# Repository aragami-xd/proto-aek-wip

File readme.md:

Yeah so this pic said it all, but I swear it's a board this time and not just a pcb

<sub>*pic credit to Pat from TapTap discord, who stole it off reddit*</sub>

<br>
<br>

### FRL

It's an FRL cuz cbf dealing with aek f row. This is like **rev 5** of the design now

pics rendered from keyshot with a *sekrit tm* design

pics from fusion. can somewhat see the mounting points and the db from the pic

<br>
<br>

### Progress
- case: pretty much done at this point
- solenoid: solenoid compartment done, solenoid driver and power delivery circuitry still sus af, db compartment kinda done
- backplate: done
- alps pcb: routing and schematic done, just need to put in the reference for the diodes and any bit of clean up left
- alps plate: probably done
- SI pcb: routing and schematic done, just need to put in the reference for the diodes and any bit of clean up left
- SI plate: not started yet, probably easy (just need to figure out stabs mount)

TODO:
- find amber alps
- find sussy aek for the caps
- make sure stuff work
- buy solenoids
- cry looking at wallet

<br>
<br>

Also credit to clickpig for naming this board "**halfpipe**". Damn the original drawing in paint was bad

Credits to:
- all snazgs memebers: phoenix (for board hunting & designing), harky & joshajohnson (for pcb), veebee (them for pcb and case designs), gok & awwyaeh (for some design inputs), pigu (for being good lad, please come back dude), clickpig (for the name lmao, and being good lad), along with many other good lads
- ai03's keyboard atelier members: zlane (for some advise and tutorials), oreo (for aek project)
- blacksimoan server members: bitten eite (for solenoid recoomendations), simoan (for the server), the recap team (for blacksimon.tv/recap), and the weeb-nsfw posters, and the vints channel regulars

Engravings (potentially):
- theremingoatimpersonator.com
- :peeposmiel: (slightly tilted) for pigu
- prototype 7frl 'halfpipe'
- ara original artisanal design craft work studio tm r c sm

Old pics of prev designs, see prev commits or the pics/old folder

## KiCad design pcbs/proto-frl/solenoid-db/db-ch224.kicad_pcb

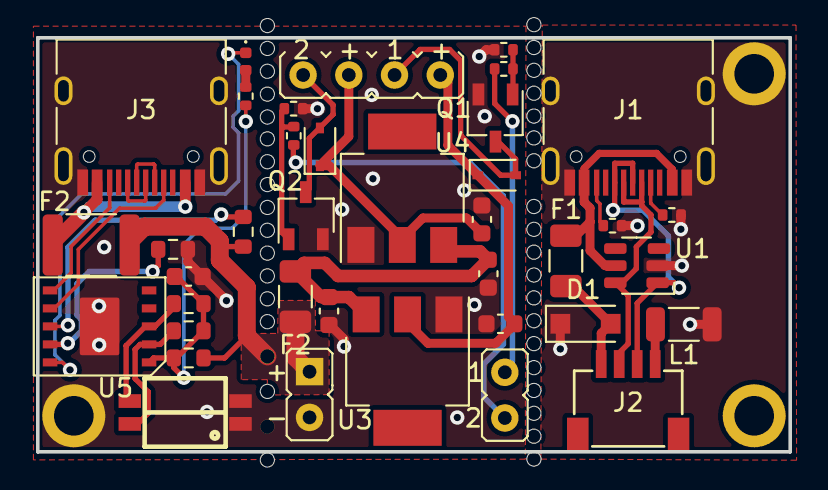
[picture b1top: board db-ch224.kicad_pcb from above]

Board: 2 copper layers, 41.8 x 23.0 mm, 38 parts (0 on the bottom side), 22 nets.

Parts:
C1, C2, C3, C4: 10uF; C_0603_1608Metric
C5: 1uF; C_0603_1608Metric
D1: SMF9.0CA; D_SOD-123F
D2, D3: 2.2k; D_SOD-323
D4: LED_0402_1005Metric
F1: 500mA; Fuse_1206_3216Metric
F2: Fuse_1812_4532Metric
F2#2: Fuse_1206_3216Metric
J1, J3#4: USB_C_Receptacle_HRO_TYPE-C-31-M-12
J2: JST-SR-4
J3: Conn_01x02_Male; PinHeader_1x4_P2.54mm_Vertical
J3#2, J3#3: Conn_01x02_Male; PinHeader_1x2_P2.54mm_Vertical
L1: L_1206_3216Metric
Q1, Q2: TSOT-23
R1, R2: 5.1k; R_0402_1005Metric
R3, R4, R5, R6: 2.2k; R_0402_1005Metric
R7: 1k; R_0603_1608Metric
R8, R10, R11, R12: 10k; R_0603_1608Metric
R9: 1k; R_0402_1005Metric
SW1: SW-SMD_4P-L3.8-W4.5-P1.27-LS6.7
U1: SRV05-4; SOT-23-6-routable
U3, U4: C26184; SOT-223
U5: CH224K; SSOP-10-1.0pitch

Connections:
+12V: C3.2, C4.2, D2.1, D3.1, J3.2, J3.4, U3.2, U4.2
CC1: J1.A5, J3#4.A5, R1.1, U5.7
CC2: J1.B5, J3#4.B5, R2.1, U5.6
CFG1: R10.2, U5.9
CFG2: R11.2, SW1.4, U5.2
CFG3: R12.2, SW1.3, U5.3
D+: J1.A6, J1.B6, J2.3, U1.1 (IO1), U5.4
D-: J1.A7, J1.B7, J2.2, U1.6 (IO4), U5.5
GND: C1.1, C2.1, C3.1, C4.1, C5.2, J2.4, J3#2.2, J3#4.A1, J3#4.A12, J3#4.B1, J3#4.B12, J3#4.S1, L1.1, Q1.2, Q2.2, R3.1, R4.1, R10.1, SW1.1, SW1.2, U3.1, U4.1, U5.0
GNDPWR: D1.1, J1.A1, J1.A12, J1.B1, J1.B12, J1.S1, L1.2, R1.2, R2.2, U1.2 (VN)
LED_PWR: D4.2, R9.2
PG: D4.1, U5.10
S1: J3#3.1, R5.1
S1_MOS: Q1.1, R3.2, R5.2
S1_OUT: D2.2, J3.3, Q1.3
S2: J3#3.2, R6.1
S2_MOS: Q2.1, R4.2, R6.2
S2_OUT: D3.2, J3.1, Q2.3
VBUS: F1.1, F2.1, J1.A4, J1.A9, J1.B4, J1.B9, J3#4.A4, J3#4.A9, J3#4.B4, J3#4.B9, U1.5 (VP)
VBUS_IN: F2.2, F2#2.1, J3#2.1, R7.1, R8.2
VCC: C1.2, C2.2, D1.2, F1.2, F2#2.2, J2.1, R8.1, U3.3, U4.3, U5.8
VDD: C5.1, R7.2, R9.1, R11.1, R12.1, U5.1

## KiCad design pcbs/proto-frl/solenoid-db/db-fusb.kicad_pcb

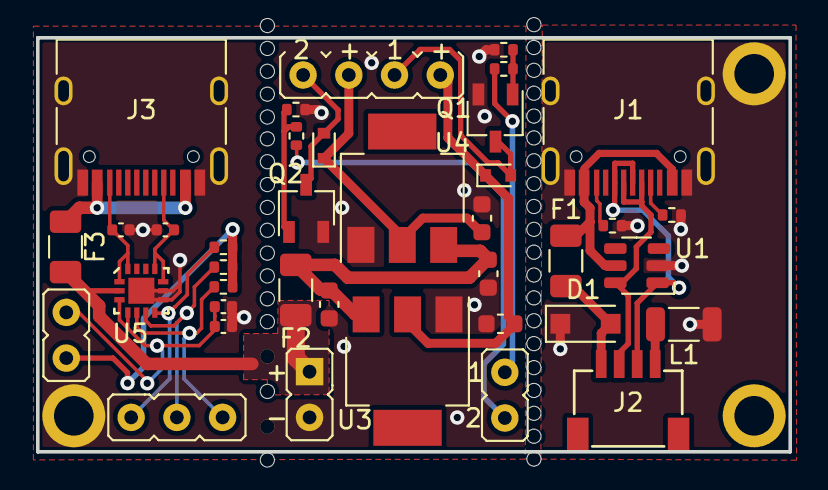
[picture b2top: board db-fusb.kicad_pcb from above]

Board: 2 copper layers, 41.8 x 23.0 mm, 38 parts (0 on the bottom side), 22 nets.

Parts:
C: C_0402_1005Metric
C1, C2, C3, C4: 10uF; C_0603_1608Metric
C5, C6: 5.1k; C_0402_1005Metric
C#2: C_0402_1005Metric
D1, D2: 2.2k; D_SOD-523
D1#2: SMF9.0CA; D_SOD-123F
F1: 500mA; Fuse_1206_3216Metric
F2, F3: Fuse_1206_3216Metric
J1, J3: USB_C_Receptacle_HRO_TYPE-C-31-M-12
J2: Conn_01x14; PinHeader_1x4_P2.54mm_Vertical
J2#2: JST-SR-4
J3#2, J3#3, J3#4: Conn_01x02_Male; PinHeader_1x2_P2.54mm_Vertical
J3#5: Conn_01x02_Male; PinHeader_1x4_P2.54mm_Vertical
L1: L_1206_3216Metric
Q1, Q2: TSOT-23
R: R_0402_1005Metric
R1, R2: 5.1k; R_0402_1005Metric
R3, R4, R5, R6: 2.2k; R_0402_1005Metric
R#2, R#3: R_0402_1005Metric
U1: SRV05-4; SOT-23-6-routable
U3, U4: C26184; SOT-223
U5: FUSB302BMPX; MLP_14

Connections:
+12V: C3.2, C4.2, D1.1, D2.1, J3#5.2, J3#5.4, U3.2, U4.2
CC1: C5.1, J1.A5, J3.A5, R1.1, U5.10, U5.11
CC2: C6.1, J1.B5, J3.B5, R2.1, U5.1, U5.14
D+: J1.A6, J1.B6, J2#2.3, U1.1 (IO1)
D-: J1.A7, J1.B7, J2#2.2, U1.6 (IO4)
GND: C.2, C1.1, C2.1, C3.1, C4.1, C5.2, C6.2, C#2.2, J2#2.4, J3.A1, J3.A12, J3.B1, J3.B12, J3.S1, J3#4.2, L1.1, Q1.2, Q2.2, R3.1, R4.1, U3.1, U4.1, U5.8, U5.9, U5.15
GNDPWR: D1#2.1, J1.A1, J1.A12, J1.B1, J1.B12, J1.S1, L1.2, R1.2, R2.2, U1.2 (VN)
INT: J2.4, R.1, U5.5
S1: J3#3.1, R5.1
S1_MOS: Q1.1, R3.2, R5.2
S1_OUT: D1.2, J3#5.3, Q1.3
S2: J3#3.2, R6.1
S2_MOS: Q2.1, R4.2, R6.2
S2_OUT: D2.2, J3#5.1, Q2.3
SCL: J2.2, R#3.1, U5.6
SDA: J2.1, R#2.1, U5.7
VBUS: F1.1, F3.1, J1.A4, J1.A9, J1.B4, J1.B9, J3.A4, J3.A9, J3.B4, J3.B9, U1.5 (VP)
VBUS_IN: F2.1, F3.2, J3#4.1, U5.2
VCC: C1.2, C2.2, D1#2.2, F1.2, F2.2, J2#2.1, U3.3, U4.3
VCONN: U5.12, U5.13
VDD: C.1, C#2.1, J3#2.1, U5.3, U5.4
V_PULLUP: J3#2.2, R.2, R#2.2, R#3.2

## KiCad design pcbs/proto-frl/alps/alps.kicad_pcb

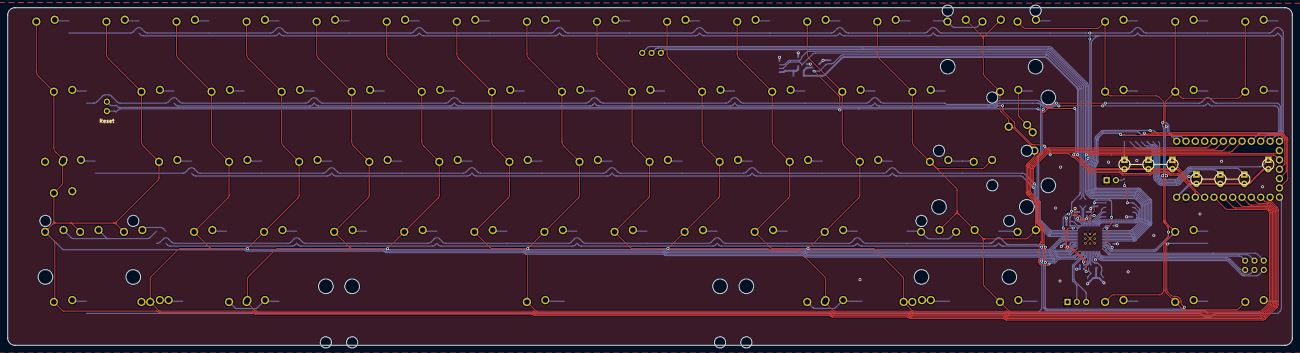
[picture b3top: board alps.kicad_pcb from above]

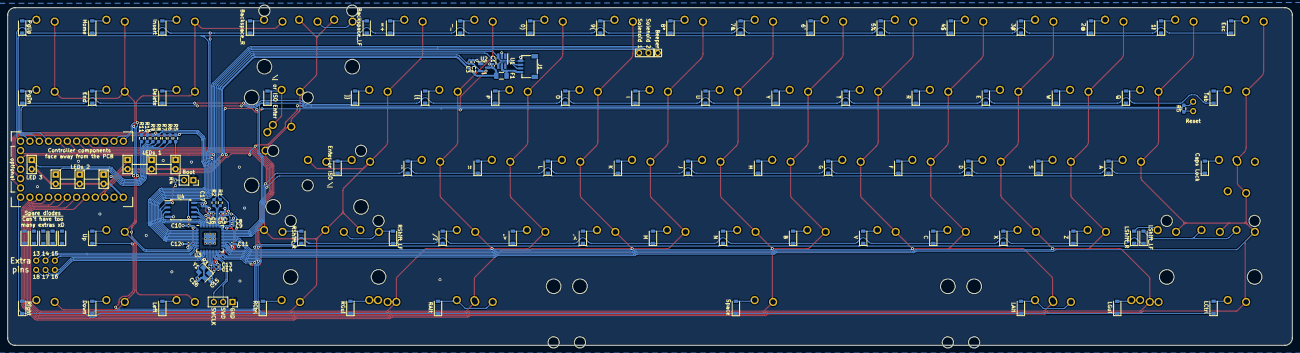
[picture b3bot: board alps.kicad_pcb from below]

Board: 2 copper layers, 349.2 x 91.8 mm, 121 parts (113 on the bottom side), 53 nets.

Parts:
0), 1!, 2@, 3#, 4$, 5%, 6^, 7&, 8*, 9(, .>: D_SOD-123
'": D_SOD-123
,<: D_SOD-123
-_: D_SOD-123
/?: D_SOD-123
;:: D_SOD-123
=+: D_SOD-123
A: D_SOD-123
B: D_SOD-123
Backspace_LF: D_SOD-123
Backspace_R: D_SOD-123
C: D_SOD-123
C1, C2, C4, C5: 1uF; C_0402_1005Metric
C3: 10uF; C_0402_1005Metric
C6, C7, C8, C9, C10, C11, C12, C13, C14, C17: 100nF; C_0402_1005Metric
C15, C16: 22pF; C_0402_1005Metric
Caps Lock: D_SOD-123
D: D_SOD-123
DDL23: LED_3mm; LED_D3.0mm-Pretty
DL11, DL12, DL13, DL21, DL22, DL31: LED_3mm; LED_D3.0mm-Pretty
Delete: D_SOD-123
Down: D_SOD-123
E: D_SOD-123
End: D_SOD-123
Enter or ISO \|: D_SOD-123
Esc: D_SOD-123
F: D_SOD-123
F1: 500mA; Fuse_1206_3216Metric
G: D_SOD-123
H: D_SOD-123
Home: D_SOD-123
I: D_SOD-123
Insert: D_SOD-123
J: D_SOD-123
J1: JST-SR-4
J2: Funny_Sound-Mask; Reset_Pretty-Mask
J3: GND; PinSocket_1x05_P2.54mm_Vertical
K: D_SOD-123
L: D_SOD-123
LAlt: D_SOD-123
LCtrl: D_SOD-123
LGui: D_SOD-123
LShift_LF: D_SOD-123
LShift_R: D_SOD-123
Left: D_SOD-123
M: D_SOD-123
N: D_SOD-123
O: D_SOD-123
P: D_SOD-123
PgDn: D_SOD-123
PgUp: D_SOD-123
Q: D_SOD-123
R: D_SOD-123
R1, R2: 27R; R_0603_1608Metric
R3, R4: 1k; R_0402_1005Metric
R5: 10k; R_0603_1608Metric_Pad0.98x0.95mm_HandSolder
R5#2, R6, R7, R8, R9, R10, R11: 1k; R_0603_1608Metric_Pad0.98x0.95mm_HandSolder
RAlt: D_SOD-123
RCtrl: D_SOD-123
RGui: D_SOD-123
RShift_LF: D_SOD-123
RShift_R: D_SOD-123
Right: D_SOD-123
S: D_SOD-123
SW0: Boot; PinSocket_1x02_P2.54mm_Vertical
SW1: Reset; PinSocket_1x02_P2.54mm_Vertical
Space: D_SOD-123
T: D_SOD-123
Tab: D_SOD-123
U: D_SOD-123
U1: SRV05-4; SOT-23-6_Handsoldering
U2: XC6206; SOT-23
U3: RP2040; RP2040-QFN-56
U4: W25Q128JVS; SOIC-8_5.23x5.23mm_P1.27mm
U5: ProMicro; pro_micro
Up: D_SOD-123
V: D_SOD-123
W: D_SOD-123
X: D_SOD-123
Y: D_SOD-123
Y1: 12MHz; Crystal_SMD_3225-4Pin_3.2x2.5mm
Z: D_SOD-123
[{: D_SOD-123
\| or ISO Enter: D_SOD-123
]}: D_SOD-123

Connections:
+1V1: C5.1, C7.1, C13.1, U3.23 (DVDD), U3.45 (VREG_VOUT), U3.50 (DVDD)
+3V3: C2.1, C3.1, C4.1, C6.1, C8.1, C9.1, C10.1, C11.1, C12.1, C14.1, C17.1, R5.1, SW1.1, U2.2 (VO), U3.1 (IOVDD), U3.10 (IOVDD), U3.22 (IOVDD), U3.33 (IOVDD), U3.42 (IOVDD), U3.43 (ADC_AVDD), U3.44 (VREG_VIN), U3.48 (USB_VDD), U3.49 (IOVDD), U4.8 (VCC), U5.4
+5V: C1.1, DDL23.2, DL11.2, DL12.2, DL13.2, DL21.2, DL22.2, DL31.2, F1.2, U2.3 (VI), U5.1
BEEPER: J2.3, U3.4 (GPIO2)
COL0: U3.30 (GPIO19), U5.11
COL1: U3.31 (GPIO20), U5.10
COL2: U3.32 (GPIO21), U5.9
COL3: U3.34 (GPIO22), U5.8
COL4: U3.35 (GPIO23), U5.7
COL5: U3.36 (GPIO24), U5.6
COL6: U3.37 (GPIO25), U5.5
COL7: U3.11 (GPIO8), U5.23
COL8: U3.12 (GPIO9), U5.24
CS: R4.2, U3.56 (QSPI_SS_N), U4.1 (~CS)
D+: R2.2, U3.47 (D+)
D-: R1.2, U3.46 (D-)
DBUS+: J1.3, R2.1, U1.3
DBUS-: J1.2, R1.1, U1.4
GND: C1.2, C2.2, C3.2, C4.2, C5.2, C6.2, C7.2, C8.2, C9.2, C10.2, C11.2, C12.2, C13.2, C14.2, C15.1, C16.1, C17.2, J1.4, J3.1, SW0.1, U1.2, U2.1 (GND), U3.19 (TESTEN), U3.57 (GND), U4.4 (GND), U5.2, U5.21, U5.22, Y1.2, Y1.4
IND1: R5#2.1, R6.1, R7.1, U3.9 (GPIO7), U5.28
IND1.1: DL11.1, R5#2.2
IND1.2: DL12.1, R6.2
IND1.3: DL13.1, R7.2
IND2: R8.1, R9.1, R10.1, U3.8 (GPIO6), U5.27
IND2.1: DL21.1, R8.2
IND2.2: DL22.1, R9.2
IND2.3: DDL23.1, R10.2
IND3: R11.1, U3.7 (GPIO5), U5.26
IND3.1: DL31.1, R11.2
QSPI_CLK: U3.52 (QSPI_SCLK), U4.6 (CLK)
RESET: R5.2, SW1.2, U3.26 (~RUN), U5.3
ROW0: 0).1, 2@.1, 4$.1, 6^.1, 8*.1, =+.1, Backspace_R.1, Esc.1, Home.1, U3.5 (GPIO3), U5.13
ROW1: 1!.1, 3#.1, 5%.1, 7&.1, 9(.1, -_.1, Backspace_LF.1, Insert.1, PgUp.1, U3.6 (GPIO4), U5.14
ROW2: Delete.1, I.1, P.1, PgDn.1, R.1, Tab.1, U3.41 (GPIO29/ADC3), U5.15, W.1, Y.1, ]}.1
ROW3: E.1, End.1, O.1, Q.1, T.1, U.1, U3.40 (GPIO28/ADC2), U5.16, [{.1, \| or ISO Enter.1
ROW4: ;:.1, Caps Lock.1, Enter or ISO \|.1, F.1, H.1, K.1, S.1, U3.39 (GPIO27/ADC1), U5.17
ROW5: '".1, A.1, D.1, G.1, J.1, L.1, U3.38 (GPIO26/ADC0), U5.18
ROW6: .>.1, B.1, C.1, LShift_LF.1, M.1, RShift_LF.1, U3.27 (GPIO16), U5.19, Up.1, Z.1
ROW7: ,<.1, /?.1, Down.1, LShift_R.1, N.1, RShift_R.1, U3.28 (GPIO17), U5.20, V.1, X.1
ROW8: LAlt.1, LCtrl.1, LGui.1, Left.1, RAlt.1, RCtrl.1, RGui.1, Right.1, Space.1, U3.29 (GPIO18), U5.12
SD0: U3.53 (QSPI_SD0), U4.5 (DI(IO0))
SD1: U3.55 (QSPI_SD1), U4.2 (DO(IO1))
SD2: U3.54 (QSPI_SD2), U4.3 (IO2)
SD3: U3.51 (QSPI_SD3), U4.7 (IO3)
SOL1: J2.1, U3.2 (GPIO0), U5.30
SOL2: J2.2, U3.3 (GPIO1), U5.29
SWCLK: J3.3, U3.24 (SWCLK)
SWD: J3.2, U3.25 (SWDIO)
USB_BOOT: R4.1, SW0.2
VBUS: F1.1, J1.1, U1.5
XTAL_0: C15.2, R3.1, Y1.1
XTAL_IN: C16.2, U3.20 (XTAL_IN), Y1.3
XTAL_OUT: R3.2, U3.21 (XTAL_OUT)

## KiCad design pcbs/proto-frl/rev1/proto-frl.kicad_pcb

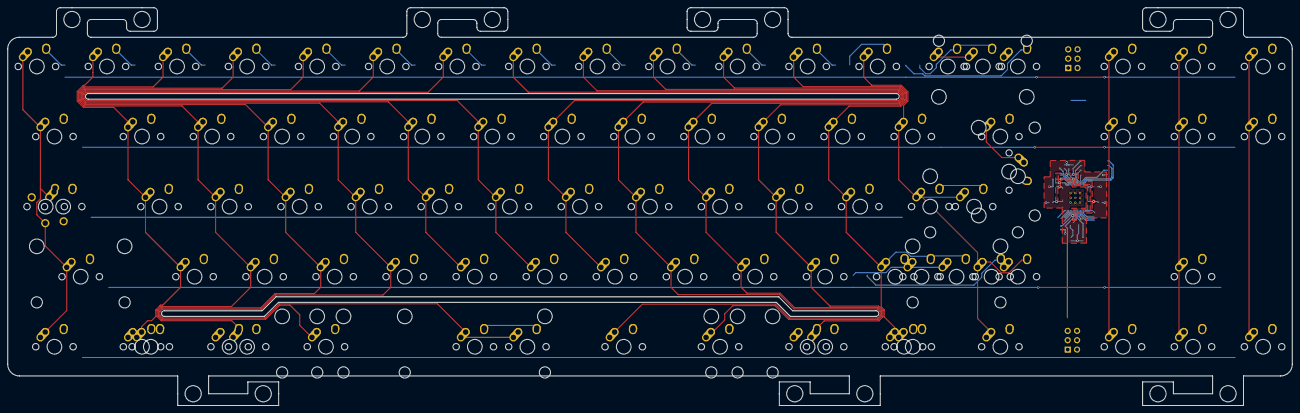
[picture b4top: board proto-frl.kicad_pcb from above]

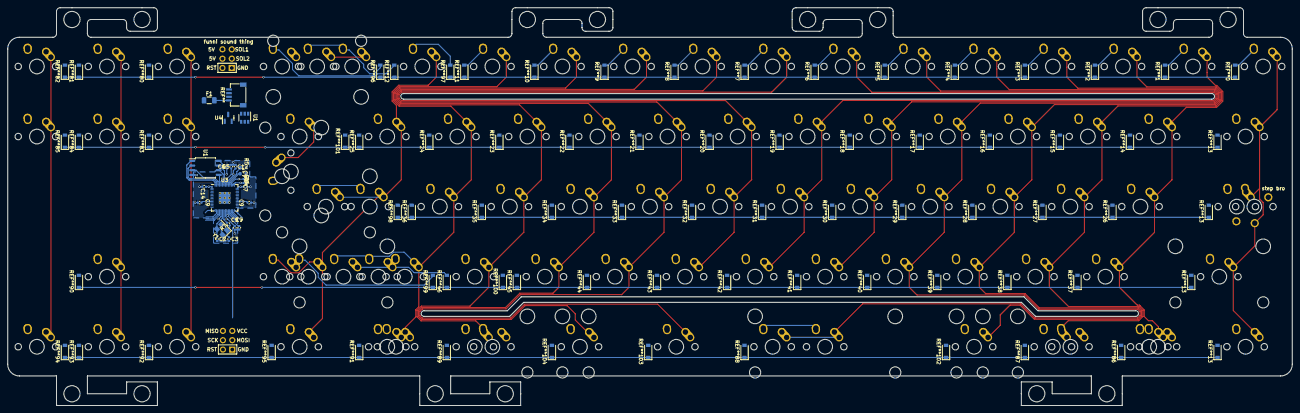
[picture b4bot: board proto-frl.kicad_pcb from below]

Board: 2 copper layers, 349.2 x 108.2 mm, 112 parts (22 on the bottom side), 28 nets.

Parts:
C2, C3: 22pF; C_0402_1005Metric
C4, C7: 1uF; C_0402_1005Metric
C5, C6, C9, C9#2, C9#3, C9#4, C12, C14, C14#2: 100nF; C_0402_1005Metric
F1: 500mA; Fuse_1206_3216Metric
MX_#0_1, MX_#1, MX_#2, MX_#3, MX_#4, MX_#5, MX_#6, MX_#7, MX_#8, MX_#9: 1U; MX-1U-NoLED
MX_'1: 1U; MX-1U-NoLED
MX_,1: 1U; MX-1U-NoLED
MX_-1: 1U; MX-1U-NoLED
MX_.1: 1U; MX-1U-NoLED
MX_/1, MX_/2: 1U; MX-1U-NoLED
MX_;1: 1U; MX-1U-NoLED
MX_=1: 1U; MX-1U-NoLED
MX_A1: 1U; MX-1U-NoLED
MX_B1: 1U; MX-1U-NoLED
MX_BACK1: 2U; MX-2U-NoLED
MX_BACK2, MX_BACK3: 1U; MX-1U-NoLED
MX_C1: 1U; MX-1U-NoLED
MX_CLOCK1: 1.75U; MX-1.75U-NoLED
MX_CLOCK2: MX-1.25U; MXOnly-1.25U-NoLED
MX_CLOCK3: MX-1.25U; ALPS-1.5U
MX_D1: 1U; MX-1U-NoLED
MX_DEL1: 1U; MX-1U-NoLED
MX_DN1: 1U; MX-1U-NoLED
MX_E1: 1U; MX-1U-NoLED
MX_END1: 1U; MX-1U-NoLED
MX_F1: 1U; MX-1U-NoLED
MX_G1: 1U; MX-1U-NoLED
MX_H1: 1U; MX-1U-NoLED
MX_HOME1: 1U; MX-1U-NoLED
MX_I1: 1U; MX-1U-NoLED
MX_INS1: 1U; MX-1U-NoLED
MX_J1: 1U; MX-1U-NoLED
MX_K1: 1U; MX-1U-NoLED
MX_L1: 1U; MX-1U-NoLED
MX_LALT2, MX_LALT3: MX-1.5U; MX-1.5U-NoLED
MX_LALT4: MX-1.5U; MX-1.25U-NoLED
MX_LALT5: MX-1.5U; MX-3U-ReversedStabilizers-NoLED
MX_LCTRL2: MX-1.5U; MX-1.5U-NoLED
MX_LFT1: 1U; MX-1U-NoLED
MX_LGUI2: MX-1U; MX-1U-NoLED
MX_LGUI3: MX-1U; MX-1.25U-NoLED
MX_LSHIFT1: 2.25U; MX-2.25U-ReversedStabilizers-NoLED
MX_M1: 1U; MX-1U-NoLED
MX_N1: 1U; MX-1U-NoLED
MX_O1: 1U; MX-1U-NoLED
MX_P1: 1U; MX-1U-NoLED
MX_PGDN1: 1U; MX-1U-NoLED
MX_PGUP1: 1U; MX-1U-NoLED
MX_Q1: 1U; MX-1U-NoLED
MX_R1: 1U; MX-1U-NoLED
MX_RALT2, MX_RALT3, MX_RALT4: 1.5U; MX-1.5U-NoLED
MX_RALT5: 1.5U; MX-1.25U-NoLED
MX_RCTRL2: 1.5U; MX-1.5U-NoLED
MX_RETURN1: 2.25U; MX-2.25U-ReversedStabilizers-NoLED
MX_RETURN2: MX-ISO; MX-ISO-ReversedStabilizers
MX_RGUI2: 1U; MX-1U-NoLED
MX_RGUI3: 1U; MX-1.25U-NoLED
MX_RSHIFT1: 2.75U; MX-2.75U-ReversedStabilizers-NoLED
MX_RSHIFT2, MX_RSHIFT4: 1.75U; MX-1.75U-NoLED
MX_RSHIFT3: 1U; MX-1U-NoLED
MX_RT1: 1U; MX-1U-NoLED
MX_S1: 1U; MX-1U-NoLED
MX_SP1: MX-7U; MX-7U-ReversedStabilizers-NoLED
MX_SP2: MX-7U; MX-10U-ReversedStabilizers-NoLED
MX_SP3: MX-7U; MX-6.5U-ReversedStabilizers-NoLED
MX_T1: 1U; MX-1U-NoLED
MX_TAB1: 1.5U; MX-1.5U-NoLED
MX_U1: 1U; MX-1U-NoLED
MX_UP1: 1U; MX-1U-NoLED
MX_V1: 1U; MX-1U-NoLED
MX_W1: 1U; MX-1U-NoLED
MX_X1: 1U; MX-1U-NoLED
MX_Y1: 1U; MX-1U-NoLED
MX_Z1: 1U; MX-1U-NoLED
MX_[1: 1U; MX-1U-NoLED
MX_\1: 1.5U; MX-1.5U-NoLED
MX_\2: 1U; MX-1U-NoLED
MX_]1: 1U; MX-1U-NoLED
MX_`1: 1U; MX-1U-NoLED
R5, R6: 27R; R_0603_1608Metric
R7: 1k; R_0402_1005Metric
U1: W25Q128JVS; SOIC-8_5.23x5.23mm_P1.27mm
U1#2: SRV05-4; SOT-23-6
U3: RP2040; RP2040-QFN-56
U4: XC6206PxxxMR-Regulator_Linear; SOT-23
Y1: 12MHz; Crystal_SMD_3225-4Pin_3.2x2.5mm

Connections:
5V: F1.1, U4.3 (VI)
+1V1: C4.1, C5.1, C9.1, U3.23 (DVDD), U3.45 (VREG_VOUT), U3.50 (DVDD)
+3V3: C6.1, C7.1, C9#2.1, C9#3.1, C9#4.1, C12.1, C14.1, C14#2.1, U1.8 (VCC), U3.1 (IOVDD), U3.10 (IOVDD), U3.22 (IOVDD), U3.33 (IOVDD), U3.42 (IOVDD), U3.43 (ADC_AVDD), U3.44 (VREG_VIN), U3.48 (USB_VDD), U3.49 (IOVDD), U4.2 (VO)
COL0: MX_CLOCK1.1, MX_CLOCK2.2, MX_CLOCK3.2, MX_LCTRL2.1, MX_LSHIFT1.1, MX_TAB1.1, MX_`1.1
COL1: MX_#1.1, MX_A1.1, MX_LGUI2.1, MX_LGUI3.1, MX_Q1.1, MX_Z1.1
COL2: MX_#2.1, MX_LALT2.2, MX_LALT3.1, MX_S1.1, MX_W1.1, MX_X1.1
COL3: MX_#3.1, MX_C1.1, MX_D1.1, MX_E1.1, MX_LALT4.1
COL4: MX_#4.1, MX_F1.1, MX_LALT5.1, MX_R1.1, MX_SP1.1, MX_V1.1
COL5: MX_#5.1, MX_B1.1, MX_G1.1, MX_T1.1
COL6: MX_#6.1, MX_H1.1, MX_N1.1, MX_Y1.1
COL7: MX_#7.1, MX_J1.1, MX_M1.1, MX_U1.1
COL8: MX_#8.1, MX_,1.1, MX_I1.1, MX_K1.1, MX_RALT5.1
COL9: MX_#9.1, MX_.1.1, MX_L1.1, MX_O1.1, MX_RALT4.1
COL10: MX_#0_1.1, MX_/1.1, MX_;1.1, MX_P1.1, MX_RALT2.1, MX_RALT3.2
COL11: MX_'1.1, MX_-1.1, MX_/2.1, MX_RGUI2.1, MX_RGUI3.1, MX_RSHIFT1.2, MX_RSHIFT2.2, MX_[1.1
COL12: MX_=1.1, MX_RCTRL2.1, MX_RETURN1.1, MX_RSHIFT3.2, MX_RSHIFT4.1, MX_\2.1, MX_]1.1
CS: U1.1 (~CS), U3.56 (QSPI_SS_N)
D+: R5.2, U1#2.1, U3.47 (D+)
D-: R6.2, U1#2.6, U3.46 (D-)
GND: C2.1, C3.1, C4.2, C5.2, C6.2, C7.2, C9.2, C9#2.2, C9#3.2, C9#4.2, C12.2, C14.2, C14#2.2, U1.4 (GND), U3.19 (TESTEN), U3.57 (GND), U4.1 (GND), Y1.2, Y1.4
QSPI_CLK: U1.6 (CLK), U3.52 (QSPI_SCLK)
SD0: U1.5 (DI(IO0)), U3.53 (QSPI_SD0)
SD1: U1.2 (DO(IO1)), U3.55 (QSPI_SD1)
SD2: U1.3 (IO2), U3.54 (QSPI_SD2)
SD3: U1.7 (IO3), U3.51 (QSPI_SD3)
XTAL_0: C3.2, R7.1, Y1.1
XTAL_IN: C2.2, U3.20 (XTAL_IN), Y1.3
XTAL_OUT: R7.2, U3.21 (XTAL_OUT)

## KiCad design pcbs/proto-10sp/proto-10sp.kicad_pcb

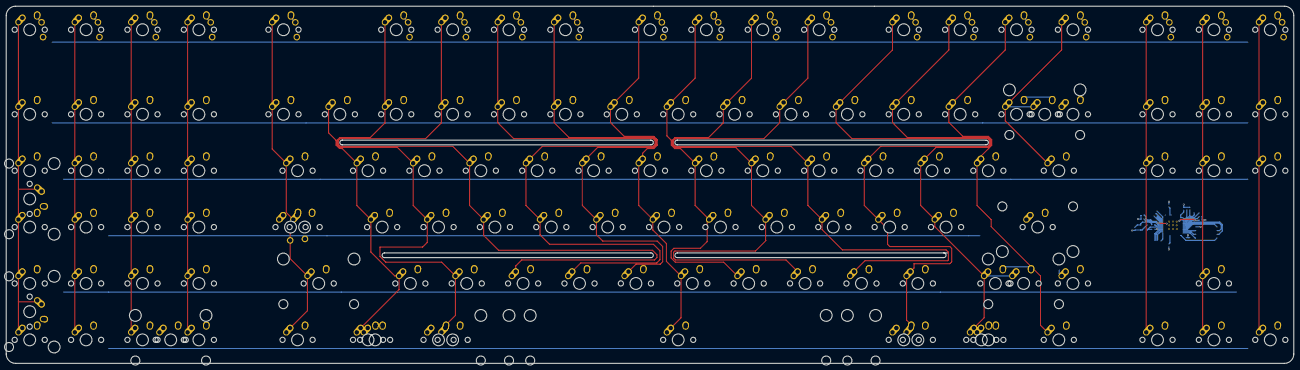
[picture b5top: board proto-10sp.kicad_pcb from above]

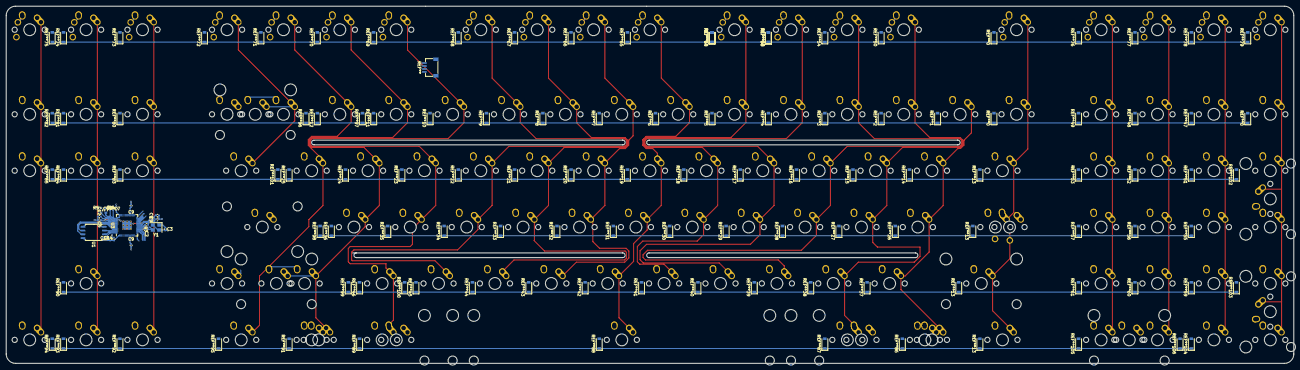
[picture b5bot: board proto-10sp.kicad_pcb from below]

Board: 2 copper layers, 435.0 x 120.7 mm, 164 parts (19 on the bottom side), 34 nets.

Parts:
C2, C3: 22pF; C_0402_1005Metric
C4, C7: 1uF; C_0402_1005Metric
C5, C9, C9#2, C9#3, C9#4, C12, C14, C14#2, C14#3: 100nF; C_0402_1005Metric
MX_#0_1, MX_#1, MX_#2, MX_#3, MX_#4, MX_#5, MX_#6, MX_#7, MX_#8, MX_#9: 1U; MX-1U-NoLED
MX_'1: 1U; MX-1U-NoLED
MX_,1: 1U; MX-1U-NoLED
MX_-1: 1U; MX-1U-NoLED
MX_.1: 1U; MX-1U-NoLED
MX_/1: 1U; MX-1U-NoLED
MX_;1: 1U; MX-1U-NoLED
MX_=1: 1U; MX-1U-NoLED
MX_A1: 1U; MX-1U-NoLED
MX_B1: 1U; MX-1U-NoLED
MX_BACK1: 2U; MX-2U-ReversedStabilizers-NoLED
MX_BACK2, MX_BACK3: 1U; MX-1U-NoLED
MX_C1: 1U; MX-1U-NoLED
MX_CLOCK1: 1.75U; MX-1.75U-NoLED
MX_CLOCK2: MX-1.25U; MX-1.25U-NoLED
MX_CLOCK3: MX-1.25U; ALPS-1.5U
MX_D1: 1U; MX-1U-NoLED
MX_DEL1: 1U; MX-1U-NoLED
MX_DN1: 1U; MX-1U-NoLED
MX_E1: 1U; MX-1U-NoLED
MX_END1: 1U; MX-1U-NoLED
MX_ESC1: 1U; MX-1U-NoLED
MX_ESC1#2, MX_ESC1#3, MX_ESC1#4, MX_ESC1#5, MX_ESC1#6: 1U; ALPS-1U
MX_F1: 1U; MX-1U-NoLED
MX_FN1, MX_FN2, MX_FN3, MX_FN4, MX_FN5, MX_FN6, MX_FN7, MX_FN8, MX_FN9, MX_FN10, MX_FN11, MX_FN12: 1U; MX-1U-NoLED
MX_FN1#2, MX_FN2#2, MX_FN3#2, MX_FN4#2, MX_FN5#2, MX_FN6#2: 1U; ALPS-1U
MX_G1: 1U; MX-1U-NoLED
MX_H1: 1U; MX-1U-NoLED
MX_HOME1: 1U; MX-1U-NoLED
MX_I1: 1U; MX-1U-NoLED
MX_INS1: 1U; MX-1U-NoLED
MX_J1: 1U; MX-1U-NoLED
MX_K1: 1U; MX-1U-NoLED
MX_L1: 1U; MX-1U-NoLED
MX_LALT2, MX_LALT3: MX-1.5U; MX-1.5U-NoLED
MX_LCTRL2: MX-1.5U; MX-1.5U-NoLED
MX_LFT1: 1U; MX-1U-NoLED
MX_LGUI2: MX-1U; MX-1U-NoLED
MX_LGUI3: MX-1U; MX-1.25U-NoLED
MX_LSHIFT1: 2.25U; MX-2.25U-ReversedStabilizers-NoLED
MX_M1: 1U; MX-1U-NoLED
MX_N1: 1U; MX-1U-NoLED
MX_NUM1, MX_NUM2, MX_NUM3, MX_NUM4, MX_NUM5, MX_NUM6, MX_NUM7, MX_NUM8, MX_NUM9, MX_NUM10, MX_NUM11, MX_NUM12, MX_NUM13, MX_NUM14, MX_NUM15, MX_NUM16, MX_NUM17, MX_NUM18, MX_NUM19, MX_NUM20, MX_NUM21, MX_NUM22, MX_NUM23, MX_NUM24: 1U; MX-1U-NoLED
MX_NUM1#2, MX_NUM1#3, MX_NUM1#4, MX_NUM1#5, MX_NUM1#6, MX_NUM1#7, MX_NUM1#8, MX_NUM1#9, MX_NUM1#10: 1U; ALPS-1U
MX_NUM_EX4, MX_NUM_EX5, MX_NUM_EX6: MX-2U; MX-2U-ReversedStabilizers-NoLED
MX_O1: 1U; MX-1U-NoLED
MX_P1: 1U; MX-1U-NoLED
MX_PAUSE1: 1U; MX-1U-NoLED
MX_PGDN1: 1U; MX-1U-NoLED
MX_PGUP1: 1U; MX-1U-NoLED
MX_PRINT1: 1U; MX-1U-NoLED
MX_Q1: 1U; MX-1U-NoLED
MX_R1: 1U; MX-1U-NoLED
MX_RALT2, MX_RALT3: 1.5U; MX-1.5U-NoLED
MX_RCTRL2: 1.5U; MX-1.5U-NoLED
MX_RETURN1: 2.25U; MX-2.25U-NoLED
MX_RGUI2: 1U; MX-1U-NoLED
MX_RGUI3: 1U; MX-1.25U-NoLED
MX_RSHIFT1: 2.75U; MX-2.75U-ReversedStabilizers-NoLED
MX_RSHIFT2: 1.75U; MX-1.75U-NoLED
MX_RSHIFT3: 1U; MX-1U-NoLED
MX_RT1: 1U; MX-1U-NoLED
MX_S1: 1U; MX-1U-NoLED
MX_SLOCK1: 1U; MX-1U-NoLED
MX_SP1: MX-7U; MX-7U-ReversedStabilizers-NoLED
MX_SP2: MX-7U; MX-10U-ReversedStabilizers-NoLED
MX_SP3: MX-7U; MX-6.5U-ReversedStabilizers-NoLED
MX_T1: 1U; MX-1U-NoLED
MX_TAB1: 1.5U; MX-1.5U-NoLED
MX_U1: 1U; MX-1U-NoLED
MX_UP1: 1U; MX-1U-NoLED
MX_V1: 1U; MX-1U-NoLED
MX_W1: 1U; MX-1U-NoLED
MX_X1: 1U; MX-1U-NoLED
MX_Y1: 1U; MX-1U-NoLED
MX_Z1: 1U; MX-1U-NoLED
MX_[1: 1U; MX-1U-NoLED
MX_\1: 1.5U; MX-1.5U-NoLED
MX_]1: 1U; MX-1U-NoLED
MX_`1: 1U; MX-1U-NoLED
R5, R6: 27R; R_0603_1608Metric
R7: 1k; R_0402_1005Metric
U1: W25Q128JVS; SOIC-8_5.23x5.23mm_P1.27mm
U3: RP2040; RP2040-QFN-56
Y1: 12MHz; Crystal_SMD_3225-4Pin_3.2x2.5mm

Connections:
+1V1: C4.1, C5.1, C9#4.1, U3.23 (DVDD), U3.45 (VREG_VOUT), U3.50 (DVDD)
+3V3: C7.1, C9.1, C9#2.1, C9#3.1, C12.1, C14.1, C14#2.1, C14#3.1, U1.8 (VCC), U3.1 (IOVDD), U3.10 (IOVDD), U3.22 (IOVDD), U3.33 (IOVDD), U3.42 (IOVDD), U3.43 (ADC_AVDD), U3.44 (VREG_VIN), U3.48 (USB_VDD), U3.49 (IOVDD)
COL0: MX_NUM1.1, MX_NUM5.1, MX_NUM9.1, MX_NUM13.1, MX_NUM17.1, MX_NUM21.1, MX_NUM_EX5.1, MX_NUM_EX6.1
COL1: MX_NUM2.1, MX_NUM6.1, MX_NUM10.1, MX_NUM14.1, MX_NUM18.1, MX_NUM22.1
COL2: MX_NUM3.1, MX_NUM7.1, MX_NUM11.1, MX_NUM15.1, MX_NUM19.1, MX_NUM23.1
COL3: MX_NUM4.1, MX_NUM8.1, MX_NUM12.1, MX_NUM16.1, MX_NUM20.1, MX_NUM24.1
COL4: MX_CLOCK1.1, MX_CLOCK2.2, MX_CLOCK3.2, MX_ESC1.1, MX_LCTRL2.1, MX_LSHIFT1.1, MX_TAB1.1, MX_`1.1
COL5: MX_#1.1, MX_A1.1, MX_LGUI2.1, MX_LGUI3.1, MX_Q1.1, MX_Z1.1
COL6: MX_#2.1, MX_FN1.1, MX_LALT2.2, MX_LALT3.1, MX_S1.1, MX_W1.1, MX_X1.1
COL7: MX_#3.1, MX_C1.1, MX_D1.1, MX_E1.1, MX_FN2.1
COL8: MX_#4.1, MX_F1.1, MX_FN3.1, MX_R1.1, MX_V1.1
COL9: MX_#5.1, MX_B1.1, MX_FN4.1, MX_G1.1, MX_T1.1
COL10: MX_#6.1, MX_FN5.1, MX_H1.1, MX_N1.1, MX_SP1.1, MX_Y1.1
COL11: MX_#7.1, MX_FN6.1, MX_J1.1, MX_M1.1, MX_U1.1
COL12: MX_#8.1, MX_,1.1, MX_FN7.1, MX_I1.1, MX_K1.1
COL13: MX_#9.1, MX_.1.1, MX_FN8.1, MX_L1.1, MX_O1.1
COL14: MX_#0_1.1, MX_/1.1, MX_;1.1, MX_FN9.1, MX_P1.1, MX_RALT2.1, MX_RALT3.2
COL15: MX_'1.1, MX_-1.1, MX_FN10.1, MX_RGUI2.1, MX_RGUI3.1, MX_RSHIFT1.1, MX_RSHIFT2.1, MX_[1.1
COL16: MX_=1.1, MX_FN11.1, MX_RCTRL2.1, MX_RSHIFT1.2, MX_RSHIFT2.2, MX_]1.1
COL17: MX_BACK1.1, MX_BACK2.1, MX_FN12.1, MX_\1.1
COL18: MX_DEL1.1, MX_INS1.1, MX_LFT1.1, MX_PRINT1.1
COL19: MX_DN1.1, MX_END1.1, MX_HOME1.1, MX_SLOCK1.1, MX_UP1.1
COL20: MX_PAUSE1.1, MX_PGDN1.1, MX_PGUP1.1, MX_RT1.1
CS: U1.1 (~CS), U3.56 (QSPI_SS_N)
D+: R5.2, U3.47 (D+)
D-: R6.2, U3.46 (D-)
GND: C2.1, C3.1, C4.2, C5.2, C7.2, C9.2, C9#2.2, C9#3.2, C9#4.2, C12.2, C14.2, C14#2.2, C14#3.2, U1.4 (GND), U3.19 (TESTEN), U3.57 (GND), Y1.2, Y1.4
SD0: U1.5 (DI(IO0)), U3.53 (QSPI_SD0)
SD1: U1.2 (DO(IO1)), U3.55 (QSPI_SD1)
SD2: U1.3 (IO2), U3.54 (QSPI_SD2)
SD3: U1.7 (IO3), U3.51 (QSPI_SD3)
XTAL_0: C3.2, R7.1, Y1.1
XTAL_IN: C2.2, U3.20 (XTAL_IN), Y1.3
XTAL_OUT: R7.2, U3.21 (XTAL_OUT)

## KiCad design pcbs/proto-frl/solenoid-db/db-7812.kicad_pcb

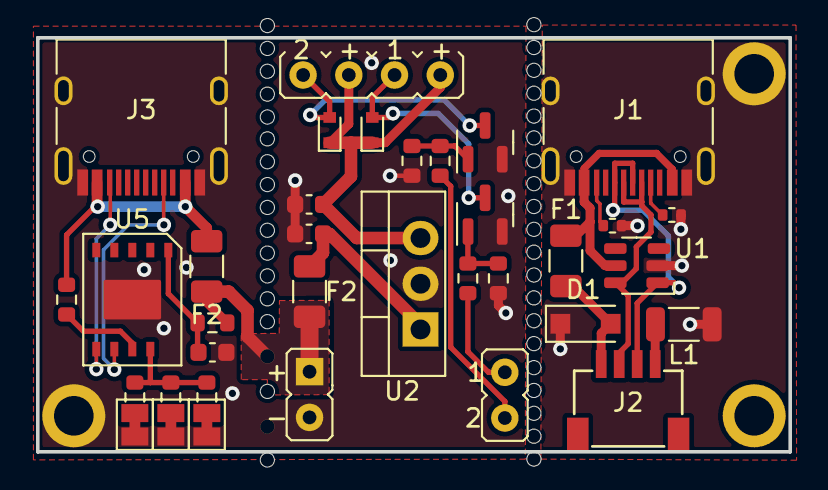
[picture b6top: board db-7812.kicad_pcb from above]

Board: 2 copper layers, 41.8 x 23.0 mm, 16 parts (0 on the bottom side), 10 nets.

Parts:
D1: SMF9.0CA; D_SOD-123F
F1: 500mA; Fuse_1206_3216Metric
F2, F2#2: Fuse_1206_3216Metric
J1, J3: USB_C_Receptacle_HRO_TYPE-C-31-M-12
J2: JST-SR-4
J3#2, J3#3: Conn_01x02_Male; PinHeader_1x2_P2.54mm_Vertical
J3#4: Conn_01x02_Male; PinHeader_1x4_P2.54mm_Vertical
L1: L_1206_3216Metric
R1, R2: 5.1k; R_0402_1005Metric
U1: SRV05-4; SOT-23-6-routable
U2: TO-220-3_Vertical
U5: CH224K; SSOP-10-1.0pitch

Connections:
+12V: J3#4.2, J3#4.4, U2.3
CC1: J1.A5, J3.A5, R1.1, U5.7
CC2: J1.B5, J3.B5, R2.1, U5.6
D+: J1.A6, J1.B6, J2.3, U1.1 (IO1)
D-: J1.A7, J1.B7, J2.2, U1.6 (IO4)
GND: J2.4, J3.A1, J3.A12, J3.B1, J3.B12, J3.S1, J3#3.2, L1.1, U2.2, U5.0
GNDPWR: D1.1, J1.A1, J1.A12, J1.B1, J1.B12, J1.S1, L1.2, R1.2, R2.2, U1.2 (VN)
VBUS: F1.1, F2#2.2, J1.A4, J1.A9, J1.B4, J1.B9, J3.A4, J3.A9, J3.B4, J3.B9, U1.5 (VP)
VBUS_IN: F2.1, F2#2.1, J3#3.1
VCC: D1.2, F1.2, F2.2, J2.1, U2.1, U5.8

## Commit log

2022-05-21 a board, i guess
2022-05-22 reworked the top, shrink down size bezels, enlarge forehead and front bezel, change pcb angles
2022-05-22 yeah nah sorry mate it's "open source", you can mess around with it however you like, but you can't gb this board without contacting me. do whatever you want with the plate tho
2022-05-27 update readme with new renders
2022-06-19 idk too many things to update just read readme
2022-09-26 no i'm not dead yet and neither is the project
2023-02-09 idk more progress after a long time
2023-02-09 cleanup repo
2023-03-20 Add via file upload cuz i'm too lazy to open terminal
